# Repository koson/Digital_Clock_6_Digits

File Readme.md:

# Digital Clock 6 Digits

## คำแนะนำ
สร้างนาฬิกา Digital 6 Digit โดยใช้อุปกรณ์ที่เรียนในวิชา เพื่อแสดงเวลาในรูปแบบ HH:MM:SS โดยใช้หลักการทำงานของวงจร Digital Logic และ Counter 

โครงงานนี้ใช้วิธีการเดินสายด้วย Wire wrapping เพื่อลดขั้นตอนในการทำ PCB และเป็นการฝึกให้นักศึกษาได้บัดกรีวงจรที่มีความซับซ้อนในระดับที่เหมาะสม

รูปตัวอย่างของบอร์ดทั้งหมด ไม่ได้เป็นข้อบังคับให้นักศึกษาต้องทำให้เหมือน อีกทั้งนักศึกษาสามารถเพิ่มเติมฟังก์ชันที่ดีกว่าต้นฉบับได้ แต่ไม่ควรน้อยกว่าเป็นอันขาด

ไฟล์ทั้งหมดที่ใช้อธิบายการทำงานและสร้างโครงงาน อยู่ในโฟลเดอร์ Documents

#### ถ้ามีข้อสงสัยหรือต้องการคำอธิบายเพิ่ม ให้เปิด issue มาได้เลยนะครับ

## 🆘 ขี้เกียจอ่านยาว ๆ  เชิญทางนี้เลยครับ [🛝](./Documents/Short-Docs.md) 

## 🆘 หรือไม่อยากอ่านเลย อยากดูคลิปอย่างเดียว  ก็เชิญทางนี้เลยครับ [🎞️](./Documents/Video-Links.md) 

---

## 📐 สถาปัตยกรรม Hardware แบบ MVC (Model-View-Controller)

โปรเจคนี้ออกแบบโดยแบ่งส่วนการทำงานออกเป็น 3 ส่วนหลักตามแนวคิด MVC:

### 🎮 **Controller** - ส่วนควบคุมและสร้างสัญญาณ Clock
- **หน้าที่:** สร้างสัญญาณนาฬิกา (Clock Signal) ที่ความถี่ 1 Hz (1 วินาที/รอบ) พร้อมทั้งสวิตช์กดเพื่อการตั้งเวลา
- **อุปกรณ์หลักส่วนกำเนิดสัญญาณนาฬิกา:** 
  - NE555 Timer ในโหมด Astable เพื่อสร้าง Clock pulse
  - LED และตัวต้านทาน  
- **ผลลัพธ์:** สัญญาณ Clock ที่มีความแม่นยำสำหรับนับเวลา สามารถสังเกตุการทำงานจากการกระพริบของ LED

- **อุปกรณ์หลักส่วนตั้งเวลาสำหรับนาฬิกา:** 
  - สวิตช์กด push button ชนิด กดติดปล่อยดับ
  - ตัวต้านทาน  Pull-up หรือ Pull Down
  - ตัวเก็บประจุ debouncing
  - SN7414 Schmitt Trigger สำหรับปรับสัญญาณให้เสถียร
  - SN7474 D Flip-Flop สำหรับสลับโหมด (RUN/SETTIME)
  - SN74LS157 Multiplexer สำหรับเลือกเส้นทางสัญญาณสำหรับโหมด  RUN และ SETTIME
- **ผลลัพธ์:** การกดปุ่มแต่ละครั้ง ไม่มี bounce และสามารถเปลี่ยนโหมด (RUN/SETTIME) และเพิ่มค่าในหลัก HH:MM:SS ครั้งละ 1 ได้ตามต้องการ 

### 📊 **Model** - ส่วนประมวลผลและนับเวลา (Counters)
- **หน้าที่:** นับและจัดเก็บค่าเวลา (ชั่วโมง นาที วินาที) ในรูปแบบ BCD
- **อุปกรณ์หลัก:**
  - SN74LS390 Decade Counter (นับเลข 0-9 และ 0-5)
- **โครงสร้างการนับ:**
  - วินาทีหลักหน่วย: 0-9 (ใช้ Counter mod-10)
  - วินาทีหลักสิบ: 0-5 (ใช้ Counter mod-6)
  - นาทีหลักหน่วย: 0-9 (ใช้ Counter mod-10)
  - นาทีหลักสิบ: 0-5 (ใช้ Counter mod-6)
  - ชั่วโมงหลักหน่วย: 0-9 (ใช้ Counter mod-10)
  - ชั่วโมงหลักสิบ: 0-2 (ใช้ Counter mod-3 สำหรับรูปแบบ 24 ชั่วโมง)

### 🖥️ **View** - ส่วนแสดงผล (7 Segments)
- **หน้าที่:** แสดงค่าเวลาออกทาง 7-Segment Display
- **อุปกรณ์หลัก:**
  - CD4543 BCD-to-7-Segment Decoder (6 ตัว สำหรับแต่ละหลัก)
  - 7-Segment Display Common Cathode (6 หลัก)
- **การทำงาน:** รับค่า BCD จาก Model แปลงเป็นรหัส 7-Segment เพื่อแสดงผลตัวเลข 0-9

---

## 🔧 การทำงานของแต่ละส่วนในโปรเจค

### 1. ส่วน Clock Generator (NE555)
- สร้างสัญญาณสี่เหลี่ยมความถี่ ~1 Hz
- ใช้สูตรคำนวณ: $f = \frac{1.44}{(R_1 + 2R_2) \times C}$
- ค่าที่ใช้: R1 = 1kΩ, R2 = 6.8kΩ, C = 100µF
- ความถี่ที่ได้: 0.986 Hz (ความคลาดเคลื่อน 1.4%)

### 2. ส่วน Counter (SN74LS390)
**วินาที:**
- Counter ตัวที่ 1: นับหลักหน่วย 0→9 (mod-10)
- Counter ตัวที่ 2: นับหลักสิบ 0→5 (mod-6)
- เมื่อครบ 59 วินาที Reset และส่งสัญญาณ Carry ไปยังส่วนนาที

**นาที:**
- Counter ตัวที่ 3: นับหลักหน่วย 0→9 (mod-10)
- Counter ตัวที่ 4: นับหลักสิบ 0→5 (mod-6)
- เมื่อครบ 59 นาที Reset และส่งสัญญาณ Carry ไปยังส่วนชั่วโมง

**ชั่วโมง:**
- Counter ตัวที่ 5: นับหลักหน่วย 0→9 (mod-10)
- Counter ตัวที่ 6: นับหลักสิบ 0→2 (mod-3)
- เมื่อครบ 23:59:59 Reset กลับเป็น 00:00:00

### 3. ส่วน Display (CD4543 + 7-Segment)
- รับสัญญาณ BCD 4 บิตจาก Counter แต่ละหลัก
- CD4543 ทำหน้าที่แปลง BCD เป็นสัญญาณควบคุม 7-Segment (a-g)
- แสดงผลตัวเลข 0-9 บน 7-Segment Display

### 4. ส่วน Time Setting
- Switch สำหรับหยุดนับและปรับเวลา
- Push Button สำหรับตั้งค่าชั่วโมง/นาที/วินาที

---

## 📁 คำอธิบายไฟล์ในโปรเจค

### 📄 Markdown Documents
- **`Readme.md`** - เอกสารหลักของโปรเจค อธิบายภาพรวมและวิธีการทำงาน
- **[`Bill-of-materials.md`](Documents/Bill-of-materials.md)** - รายการอุปกรณ์ที่ใช้ในโปรเจค
- **[`Construction-Process.md`](Construction-Process-Display.md)** - ขั้นตอนการประกอบวงจรตามลำดับ
- **[`Datasheets.md`](Documents/Datasheets.md)** - รายละเอียด Datasheet ของ IC ที่ใช้ในวงจร
- **[`Kicad-Setup.md`](Documents/Kicad-Setup.md)** - คู่มือการตั้งค่าและใช้งาน KiCad
- **[`NE555_Clock.md`](NE555-Clock-Generator.md)** - การคำนวณและออกแบบวงจร NE555

### 🔌 Circuit Files (โฟลเดอร์ Circuit/)
- **[`Digital_Clock_6_Digits.kicad_pro`](Circuit/Digital_Clock_6_Digits.kicad_pro)** - ไฟล์โปรเจค KiCad หลัก
- **[`Digital_Clock_6_Digits.kicad_sch`](Circuit/Digital_Clock_6_Digits.kicad_sch)** - Schematic หลักที่เชื่อมโยงส่วนย่อย
- **[`Controller.kicad_sch`](Circuit/Controller.kicad_sch)** - วงจร NE555 Clock Generator
- **[`Counter.kicad_sch`](Circuit/Counter.kicad_sch)** - วงจร Counter ทุกหลัก (วินาที นาที ชั่วโมง)
- **[`7Seg_6Digits.kicad_sch`](Circuit/7Seg_6Digits.kicad_sch)** - วงจร Decoder และ Display 6 หลัก
- **[`Seven_Segment_View.kicad_sch`](Circuit/Seven_Segment_View.kicad_sch)** - มุมมองการเชื่อมต่อ 7-Segment
- **[`Digital_Clock_6_Digits.kicad_pcb`](Circuit/Digital_Clock_6_Digits.kicad_pcb)** - ไฟล์ออกแบบ PCB
- **[`Library.kicad_sym`](Circuit/Library.kicad_sym)** - ไลบรารีสัญลักษณ์ที่ใช้ในโปรเจค
- **[`Digital_Clock_6_Digits.csv`](Circuit/Digital_Clock_6_Digits.csv)** - Bill of Materials จาก KiCad

---

## 🛠️ ลำดับขั้นตอนการทำโปรเจค

``` mermaid
%%{init: {'theme':'base', 'flowchart': {'padding': 20, 'nodeSpacing': 50, 'rankSpacing': 50}, 'themeVariables': {'fontSize':'13px', 'fontFamily':'Arial'}}}%%
flowchart TD
    Phase1["Study documentation"] --> Phase2["Study schematic in Kicad"]
    Phase2 --> Phase3["Acquire components"]   

    subgraph "building circuit"
        direction TB
        Phase4
        Phase5
        Phase6
    end
    Phase3 --> Phase4["Build Display circuit"]
    Phase4 --> Phase5["Build Counter circuit"]
    Phase5 --> Phase6["Build Controller circuit"]
    Phase6 --> Phase7["Test and Debug"]
    Phase7 --> Phase7-1{"Does it work?"}
    Phase7-1 -->|Yes| Phase8["Document and Publish"]
    Phase7-1 -->|No| Phase3["Acquire components"]
```

### Phase 1: ศึกษาเอกสารต่างๆ (เริ่มจากไฟล์ Readme.md)
- [ ] **ศึกษา Datasheet** ของ IC แต่ละตัวให้เข้าใจการทำงาน โดยเฉพาะ:
	- [ ] CD4543 (BCD-to-7-Segment Decoder)
	- [ ] SN74LS390 (Decade Counter)
	- [ ] NE555 (Timer)
	- [ ] SN74LS157 (Multiplexer)

- [ ] **ศึกษาวงจรย่อย** แต่ละส่วนที่อาจารย์ให้ไว้:
	- [ ] วงจร Clock Generator (NE555)
	- [ ] วงจร Counter (SN74LS390) สำหรับ วินาที นาที ชั่วโมง
    - [ ] วงจร Display (CD4543 + 7-Segment)

- [ ]  **คำนวณค่าอุปกรณ์:** ถ้าอุปกรณ์ที่หามาได้ไม่ตรงกับค่าในวงจร 
	- [ ]  คำนวณ R และ C สำหรับ NE555 ให้ได้ความถี่ 1 Hz
	- [ ]  ตรวจสอบ Duty Cycle ให้อยู่ในช่วง 40-60%

### Phase 2: ศึกษาวงจรใน KiCad (ต้องลงโปรแกรม KiCad)
- [ ] **สร้าง Schematic แยกตามส่วน:**
    - [ ] `Controller.kicad_sch` - วงจร NE555
    - [ ] `Counter.kicad_sch` - วงจรนับเวลา
    - [ ] `7Seg_6Digits.kicad_sch` - วงจรแสดงผล
    - [ ] `Digital_Clock_6_Digits.kicad_sch` - เชื่อมโยงทุกส่วนเข้าด้วยกัน

- [ ] **ตรวจสอบความถูกต้อง:**
    - [ ] ตรวจสอบการเชื่อมต่อระหว่างส่วน
    - [ ] ตรวจสอบ Power Supply (VCC, GND)
    - [ ] ใช้มัลติมิเตอร์ตรวจสอบข้อผิดพลาด

### Phase 3: จัดหาอุปกรณ์ตามรายการ
- [ ] **จัดทำรายการอุปกรณ์ (BOM - Bill of Materials):**
    - [ ] IC ทั้งหมดตาม Schematic (CD4543, SN74LS390, NE555, SN74LS157, SN7414, SN7474)
    - [ ] 7-Segment Display Common Cathode 6 หลัก ควรใส่ Socket หรือ connector ตามคำแนะนำในการประกอบวงจร
    - [ ] ตัวต้านทาน (Resistor) ค่าต่างๆ ตามที่คำนวณไว้ในวงจร
    - [ ] ตัวเก็บประจุ (Capacitor) สำหรับวงจร NE555 และ Decoupling
    - [ ] แผ่นวงจรเอนกประสงค์ (Universal PCB) ขนาดที่เหมาะสม
    - [ ] IC Socket สำหรับ IC ทุกตัว (แนะนำให้ใช้เพื่อความสะดวกในการเปลี่ยน IC)
    - [ ] สาย Wire Wrap หรือสายเดินสายแบบอ่อน (Jumper Wire)
    - [ ] Push Button Switch สำหรับตั้งค่าเวลา
    - [ ] LED สำหรับแสดงสถานะ Clock
    - [ ] แหล่งจ่ายไฟ 5V (Adapter หรือ Battery)

- [ ] **ตรวจสอบอุปกรณ์:**
    - [ ] ตรวจสอบความถูกต้องของ IC ทุกตัวด้วย Datasheet
    - [ ] ทดสอบค่าตัวต้านทานและตัวเก็บประจุด้วย Multimeter
    - [ ] ตรวจสอบ 7-Segment Display ว่าเป็น Common Cathode
    - [ ] เตรียมอุปกรณ์สำรอง (IC, ตัวต้านทาน, สาย) กรณีชำรุด

### Phase 4: ประกอบส่วน Display
- [ ] **เตรียมอุปกรณ์สำหรับส่วน Display:**
    - [ ] IC Socket สำหรับ CD4543 (6 ตัว)
    - [ ] CD4543 BCD-to-7-Segment Decoder (6 ตัว)
    - [ ] 7-Segment Display Common Cathode (6 หลัก)
    - [ ] ตัวต้านทาน Current Limiting สำหรับ LED แต่ละ Segment
    - [ ] แผ่นวงจรเอนกประสงค์ขนาดพอเหมาะ

- [ ] **วางตำแหน่ง Component:**
    - [ ] วาง 7-Segment Display ให้เรียงตามลำดับ (HH:MM:SS)
    - [ ] วาง IC Socket สำหรับ CD4543 ไว้ใกล้กับ 7-Segment แต่ละหลัก
    - [ ] วางตำแหน่งให้พิจารณาเส้นทางการเดินสายไปยัง Counter (ส่วนถัดไป)
    - [ ] สามารถวางตามตัวอย่างในรูปชิ้นงานที่สำเร็จแล้วได้ 

- [ ] **บัดกรี Component:**
    - [ ] บัดกรี 7-Segment Display ทั้ง 6 หลัก ตรวจสอบให้แน่ใจว่าหลักตรง
    - [ ] บัดกรี IC Socket สำหรับ CD4543 ทั้ง 6 ตัว ตรวจสอบทิศทางขา 1
    - [ ] บัดกรีตัวต้านทาน Current Limiting สำหรับแต่ละ Segment

- [ ] **เดินสายด้วย Wire Wrap:**
    - [ ] เชื่อมต่อสาย VCC และ GND ให้ทุก IC (ควรเดินสายเป็นแนว Bus)
    - [ ] เชื่อมต่อสาย Output a-g จาก CD4543 ไปยัง 7-Segment แต่ละหลัก
    - [ ] เชื่อมต่อขา Common Cathode ของ 7-Segment ทั้งหมดไปยัง GND
    - [ ] เตรียมจุดต่อสำหรับสาย Input BCD (4 บิต) จากส่วน Counter

- [ ] **ทดสอบส่วน Display:**
    - [ ] **ยังไม่ต้องใส่ CD4543 ลงใน IC Socket**
    - [ ] จ่ายไฟ 5V ตรวจสอบแรงดันที่ขาไฟเลี้ยงและ ground ของ IC ทุกตัว
    - [ ] ถ้าวัดไฟแล้วไม่มีอะไรผิดพลาด ให้ปลดไฟเลี้ยงออกแล้วเสียบ IC ลงไปใน socket โดยทำจากหลักวินาทีเพียงตัวเดียวก่อน
    - [ ] จ่ายไฟเข้าวงจร IC ต้องไม่ร้อนกว่าปกติ วัดแรงดันไฟเลี้ยงควรได้เท่ากับตอนที่ยังไม่เสียบ IC 
    - [ ] ทดสอบการแสดงผลด้วยการจ่ายสัญญาณ BCD แบบ Manual (ใช้สวิตช์หรือสาย Jumper)
    - [ ] ตรวจสอบว่าแต่ละหลักสามารถแสดงตัวเลข 0-9 ได้ถูกต้อง
    - [ ] บันทึกปัญหาที่พบ (ถ้ามี) เช่น Segment ที่ไม่ติด

### Phase 5: ประกอบส่วน Counter
- [ ] **เตรียมอุปกรณ์สำหรับส่วน Counter:**
    - [ ] IC Socket สำหรับ SN74LS390 (3 ตัว สำหรับ วินาที นาที ชั่วโมง)
    - [ ] SN74LS390 Dual Decade Counter (3 ตัว)
    - [ ] ตัวเก็บประจุ Decoupling 0.1µF สำหรับแต่ละ IC
    - [ ] แผ่นวงจรเอนกประสงค์ขนาดพอเหมาะ (หรือใช้แผ่นเดียวกับ Display)

- [ ] **วางตำแหน่ง Component:**
    - [ ] วาง IC Socket สำหรับ Counter ตามลำดับ: วินาที → นาที → ชั่วโมง
    - [ ] วางให้สะดวกต่อการเชื่อมต่อกับส่วน Display และ Controller
    - [ ] คำนึงถึงการเดินสายระหว่าง Counter แต่ละหลัก (Cascade)
    - [ ] สามารถวางตำแหน่งตามในรูปวงจรต้นแบบได้

- [ ] **บัดกรี Component:**
    - [ ] บัดกรี IC Socket สำหรับ SN74LS390 ทั้ง 3 ตัว
    - [ ] บัดกรีตัวเก็บประจุ Decoupling ไว้ใกล้ขา VCC และ GND ของแต่ละ IC
    - [ ] บัดกรี IC Logic Gate เพิ่มเติม (ถ้ามี) สำหรับวงจร Reset

- [ ] **เดินสายด้วย Wire Wrap:**
    - [ ] เชื่อมต่อสาย VCC และ GND ให้ทุก IC
    - [ ] **วงจรวินาที:** บัดกรีวงจรตามที่แสดงใน Kicad
        - [ ] เชื่อมต่อ Clock Input สำหรับนับวินาทีหลักหน่วย (0-9)
        - [ ] เชื่อมต่อ Carry Output ไปยังหลักสิบ (0-5)
        - [ ] ต่อขา Output BCD (4 บิต) ของทั้ง 2 หลักไปยังส่วน Display
        - [ ] ต่อวงจร Reset เมื่อครบ 59 → 00
    - [ ] **วงจรนาที:** บัดกรีวงจรตามที่แสดงใน Kicad
        - [ ] รับ Clock Input จาก Carry ของวินาทีหลักสิบ
        - [ ] เชื่อมต่อ Carry Output ไปยังหลักสิบ (0-5)
        - [ ] ต่อขา Output BCD ไปยังส่วน Display
        - [ ] ต่อวงจร Reset เมื่อครบ 59 → 00
    - [ ] **วงจรชั่วโมง:** บัดกรีวงจรตามที่แสดงใน Kicad
        - [ ] รับ Clock Input จาก Carry ของนาทีหลักสิบ
        - [ ] เชื่อมต่อหลักหน่วย (0-9) และหลักสิบ (0-2)
        - [ ] ต่อขา Output BCD ไปยังส่วน Display
        - [ ] ต่อวงจร Reset เมื่อครบ 23 → 00 (รูปแบบ 24 ชั่วโมง)

- [ ] **เชื่อมต่อส่วน Display เข้ากับ Connector ทั้ง 6 ตัว:**
    - [ ] ต่อสาย BCD Output จาก Counter แต่ละหลักไปยัง Input ของ CD4543
    - [ ] ตรวจสอบความถูกต้องของการต่อสาย (bit 0-3)

- [ ] **ทดสอบส่วน Counter:**
    - [ ] ใส่ IC SN74LS390 ลงใน IC Socket ทุกตัว
    - [ ] จ่ายไฟ 5V และตรวจสอบแรงดันที่ IC ทุกตัว
    - [ ] จ่ายสัญญาณ Clock แบบ Manual (กดปุ่มหรือใช้ Switch)
    - [ ] ตรวจสอบการนับของวินาที: 00 → 01 → ... → 09 → 10 → ... → 59 → 00
    - [ ] ตรวจสอบ Carry Signal ส่งต่อไปยังนาทีเมื่อวินาทีครบ 59
    - [ ] ตรวจสอบการนับของนาทีและชั่วโมงแบบเดียวกัน
    - [ ] ตรวจสอบว่าเมื่อครบ 23:59:59 แล้ว จะ Reset เป็น 00:00:00

### Phase 6: ประกอบส่วน Controller (Clock Generator และ Time Setting)
- [ ] **เตรียมอุปกรณ์สำหรับส่วน Controller:**
    - [ ] IC Socket สำหรับ NE555, SN7414, SN7474, SN74LS157
    - [ ] NE555 Timer IC
    - [ ] SN7414 Schmitt Trigger (สำหรับปรับสัญญาณ)
    - [ ] SN7474 D Flip-Flop (สำหรับสลับโหมด RUN/SETTIME)
    - [ ] SN74LS157 Multiplexer (สำหรับเลือกสัญญาณ Clock)
    - [ ] ตัวต้านทาน 1kΩ, 6.8kΩ (หรือค่าที่คำนวณได้)
    - [ ] ตัวเก็บประจุ 100µF (หรือค่าที่คำนวณได้)
    - [ ] Push Button Switch (สำหรับ Mode Switch, Hour, Minute, Second)
    - [ ] LED สำหรับแสดงสถานะ Clock และโหมด
    - [ ] ตัวต้านทาน Pull-up/Pull-down สำหรับปุ่ม
    - [ ] ตัวเก็บประจุ Debouncing สำหรับปุ่มกด
    - [ ] แผ่นวงจรเอนกประสงค์ขนาดพอเหมาะ

- [ ] **ส่วน Clock Generator (NE555):**
    - [ ] บัดกรี IC Socket สำหรับ NE555
    - [ ] บัดกรีตัวต้านทาน R1 (1kΩ) และ R2 (6.8kΩ)
    - [ ] บัดกรีตัวเก็บประจุ C (100µF)
    - [ ] บัดกรี LED และตัวต้านทาน Current Limiting
    - [ ] เดินสายตาม Schematic ของ NE555 Astable Mode
    - [ ] เชื่อม Output ของ NE555 ไปยัง SN7414 (Schmitt Trigger)

- [ ] **ส่วน Time Setting:**
    - [ ] บัดกรี Push Button ทั้งหมด (Mode, Hour, Minute, Second)
    - [ ] บัดกรีตัวต้านทาน Pull-up/Pull-down สำหรับปุ่มแต่ละตัว
    - [ ] บัดกรีตัวเก็บประจุ Debouncing ควบคู่กับปุ่ม
    - [ ] บัดกรี IC Socket สำหรับ SN7414, SN7474, SN74LS157
    - [ ] เดินสาย Output จากปุ่มผ่าน SN7414 เพื่อปรับสัญญาณให้เสถียร
    - [ ] เดินสายจาก SN7474 เพื่อสลับระหว่างโหมด RUN และ SETTIME
    - [ ] เดินสายจาก SN74LS157 เพื่อเลือก Clock Source:
        - [ ] โหมด RUN: ใช้สัญญาณจาก NE555 (1 Hz)
        - [ ] โหมด SETTIME: ใช้สัญญาณจากปุ่มกด (Manual Clock)

- [ ] **เชื่อมต่อกับส่วน Counter:**
    - [ ] ต่อ Output จาก Multiplexer (SN74LS157) ไปยัง Clock Input ของ Counter
    - [ ] ต่อสัญญาณจากปุ่ม Hour, Minute, Second ไปยัง Clock Input ของ Counter ที่เกี่ยวข้อง (ผ่าน Multiplexer)

- [ ] **ทดสอบส่วน Controller:**
    - [ ] **ทดสอบ NE555 Clock Generator:**
        - [ ] จ่ายไฟ 5V และสังเกตการกระพริบของ LED
        - [ ] ถ้าสามารถ ให้วัดความถี่ด้วย Oscilloscope หรือ Frequency Counter (ควรได้ ~1 Hz)
        - [ ] ถ้าสามารถ ให้วัด Duty Cycle ควรอยู่ในช่วง 40-60%
    - [ ] **ทดสอบ Push Button และ Debouncing:**
        - [ ] กดปุ่มแต่ละตัวและตรวจสอบว่าไม่มี Bounce (อาจจะใช้ Oscilloscope หรือ Logic Probe แต่จากการออกแบบวงจร ไม่ควรจะเกิด bounce ถ้าบัดกรีถูกต้อง)
        - [ ] ตรวจสอบว่า Schmitt Trigger ทำงานถูกต้อง
    - [ ] **ทดสอบ Mode Switch (RUN/SETTIME):**
        - [ ] กดปุ่ม Mode และตรวจสอบว่า D Flip-Flop สลับสถานะ
        - [ ] ตรวจสอบว่า LED แสดงโหมดปัจจุบัน (RUN หรือ SETTIME)
    - [ ] **ทดสอบ Multiplexer:**
        - [ ] ในโหมด RUN: Counter ต้องนับตามสัญญาณจาก NE555 (1 วินาที/ครั้ง)
        - [ ] ในโหมด SETTIME: การกดปุ่ม Hour/Minute/Second ต้องเพิ่มค่าในหลักที่ถูกต้อง

### Phase 7: การทดสอบและแก้ไขปัญหา (Testing & Debugging)
- [ ] **ทดสอบการทำงานของแต่ละส่วนร่วมกัน:**
    - [ ] เชื่อมต่อทุกส่วนเข้าด้วยกัน: Controller → Counter → Display
    - [ ] จ่ายไฟ 5V และตรวจสอบแรงดันที่ IC ทุกตัว (ควรได้ 4.75-5.25V)
    - [ ] สังเกตการแสดงผลบน 7-Segment Display

- [ ] **ทดสอบโหมด RUN (การทำงานปกติ):**
    - [ ] ตั้งเวลาเริ่มต้นเป็น 00:00:00
    - [ ] สังเกตการนับวินาที ควรเพิ่มทีละ 1 ทุกวินาที
    - [ ] ตรวจสอบการ Carry: 00:00:59 → 00:01:00, 00:59:59 → 01:00:00
    - [ ] ทดสอบการ Reset เมื่อครบ 23:59:59 → 00:00:00
    - [ ] ให้วงจรทำงานต่อเนื่อง 1-2 ชั่วโมง เพื่อตรวจสอบความเสถียร

- [ ] **ทดสอบโหมด SETTIME (การตั้งเวลา):**
    - [ ] กดปุ่ม Mode เพื่อเข้าสู่โหมด SETTIME
    - [ ] กดปุ่ม Hour และตรวจสอบว่าชั่วโมงเพิ่มขึ้น
    - [ ] กดปุ่ม Minute และตรวจสอบว่านาทีเพิ่มขึ้น
    - [ ] กดปุ่ม Second และตรวจสอบว่าวินาทีเพิ่มขึ้น
    - [ ] กดปุ่ม Mode อีกครั้งเพื่อกลับสู่โหมด RUN
    - [ ] ตรวจสอบว่านาฬิกานับต่อจากเวลาที่ตั้งไว้

- [ ] **ทดสอบความแม่นยำของเวลา:**
    - [ ] เปรียบเทียบกับนาฬิกามาตรฐาน (นาฬิกาข้อมือ, โทรศัพท์)
    - [ ] ให้วงจรทำงานต่อเนื่อง 24 ชั่วโมง
    - [ ] วัดความคลาดเคลื่อนของเวลา (ควรไม่เกิน ±1-2 นาที/วัน)
    - [ ] หากความคลาดเคลื่อนมาก ให้ปรับค่า R หรือ C ของ NE555

- [ ] **การแก้ไขปัญหาทั่วไป:**
    - [ ] **Display ไม่แสดงผล:**
        - [ ] ตรวจสอบการต่อขา IC และ 7-Segment
        - [ ] ตรวจวัดแรงดันที่ขา VCC และ GND
        - [ ] ตรวจสอบตัวต้านทาน Current Limiting
    - [ ] **Counter นับไม่ถูกต้อง:**
        - [ ] ตรวจสอบสัญญาณ Clock ด้วย Oscilloscope หรือ Logic Probe
        - [ ] ตรวจสอบวงจร Reset (อาจ Reset บ่อยเกินไปหรือไม่ Reset)
        - [ ] ตรวจสอบการต่อ Carry Signal ระหว่าง Counter
    - [ ] **Clock ความถี่ไม่ถูกต้อง:**
        - [ ] วัดค่าจริงของ R และ C ด้วย Multimeter
        - [ ] คำนวณความถี่ใหม่และปรับค่า R หรือ C
        - [ ] ตรวจสอบการต่อวงจร NE555
    - [ ] **ปุ่มกดมี Bounce:**
        - [ ] เพิ่มตัวเก็บประจุ Debouncing (0.1-1µF)
        - [ ] ตรวจสอบวงจร Schmitt Trigger
    - [ ] **นาฬิกาหยุดทำงานหลังทำงานได้สักพัก:**
        - [ ] ตรวจสอบการบัดกรีที่หลวม (Cold Solder Joint)
        - [ ] ตรวจสอบแหล่งจ่ายไฟว่ามีกระแส (Current) เพียงพอ
        - [ ] เพิ่มตัวเก็บประจุ Decoupling ที่ IC ทุกตัว

### Phase 8: เอกสารและการสรุปผล (Documentation)
- [ ] **ถ่ายภาพและวิดีโอ:**
    - [ ] ถ่ายภาพวงจรที่ประกอบเสร็จจากหลายมุม
    - [ ] ถ่ายภาพ Close-up ของแต่ละส่วนสำคัญ (Display, Counter, Controller)
    - [ ] ถ่ายภาพการเดินสายด้วย Wire Wrap
    - [ ] ถ่ายวิดีโอการทำงานของนาฬิกา ให้เห็นการเปลี่ยนวินาที 57 --> 58 --> 59 --> 00 --> 01 (อย่างน้อย 5 นาที) ทั้งในหลัก วินาที  --> นาที, นาที --> ชั่วโมง และเมื่อเปลี่ยน 23:59:xx ไปเป็น 00:00:xx
    - [ ] ถ่ายวิดีโอการตั้งเวลา (แสดงการใช้งานปุ่มกด)

- [ ] **บันทึกข้อมูลทางเทคนิค:**
    - [ ] รายการ IC ทั้งหมดที่ใช้พร้อมรุ่นและจำนวน
    - [ ] ค่าตัวต้านทานและตัวเก็บประจุที่ใช้จริง
    - [ ] ค่าความถี่ของ Clock ที่วัดได้
    - [ ] ความคลาดเคลื่อนของเวลาที่วัดได้
    - [ ] BOM (Bill of Materials) ฉบับสมบูรณ์

- [ ] **บันทึกปัญหาและวิธีแก้ไข:**
    - [ ] ปัญหาที่พบระหว่างการประกอบและทดสอบ
    - [ ] วิธีการแก้ไขปัญหาแต่ละอย่าง
    - [ ] ข้อผิดพลาดที่เกิดขึ้นและบทเรียนที่ได้รับ
    - [ ] คำแนะนำสำหรับผู้ที่จะทำโปรเจคนี้ต่อไป

- [ ] **เขียนเอกสารสรุป:**
    - [ ] วัตถุประสงค์ของโปรเจค
    - [ ] หลักการทำงานของนาฬิกา Digital
    - [ ] การออกแบบวงจรและการคำนวณ
    - [ ] ขั้นตอนการประกอบโดยสังเขป
    - [ ] ผลการทดสอบและประเมินความสำเร็จ
    - [ ] สรุปและข้อเสนอแนะ

- [ ] **เผยแพร่บน GitHub (ถ้าต้องการ):**
    - [ ] อัพโหลดไฟล์ Schematic (KiCad)
    - [ ] อัพโหลดรูปภาพ
    - [ ] อัพโหลดวิดีโอขึ้น YouTube และแปะลิ้งค์ไว้บน Github
    - [ ] อัพเดต README.md ให้มีข้อมูลครบถ้วน
    - [ ] เพิ่ม Bill of Materials (BOM)
    - [ ] เพิ่มคู่มือการประกอบ (Construction Process)
    - [ ] เขียน License และ Contributors
    - [ ] เปิดให้ผู้สนใจสามารถเปิด Issue หรือ Pull Request ได้

---

## 📚 เอกสารอ้างอิง
- [Bill of Materials](./Documents/Bill-of-materials.md) - รายการอุปกรณ์
- [Construction Process](./Documents/Construction-Process-Display.md) - ขั้นตอนการประกอบ
- [Datasheets](./Documents/Datasheets.md) - ข้อมูล IC ที่ใช้
- [NE555 Clock Calculation](./Documents/NE555-Clock-Generator.md) - การคำนวณวงจร Clock

---

## วงจรที่ประกอบสำเร็จแล้ว

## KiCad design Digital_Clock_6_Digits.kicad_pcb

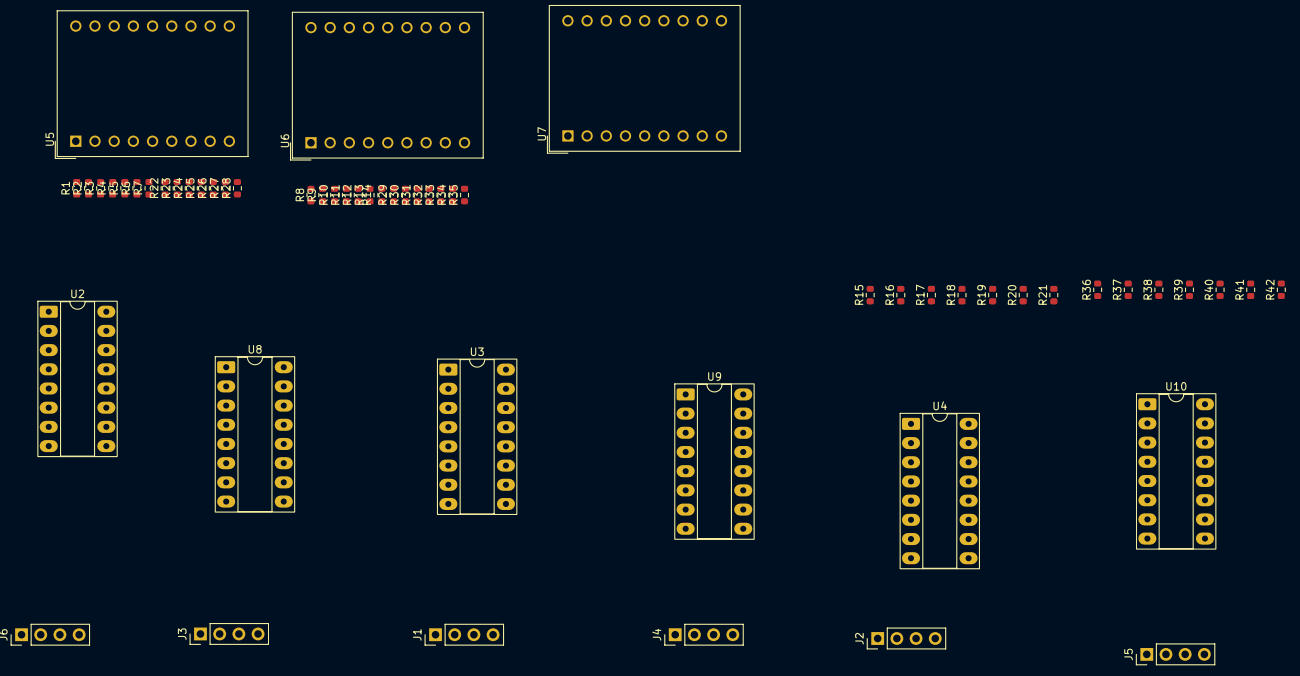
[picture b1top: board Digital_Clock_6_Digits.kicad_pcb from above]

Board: 2 copper layers, 57 parts (0 on the bottom side), 110 nets, no tracks yet.

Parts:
J1, J2, J3, J4, J5, J6: Conn_01x04; PinHeader_1x04_P2.54mm_Vertical
R1, R2, R3, R4, R5, R6, R7, R8, R9, R10, R11, R12, R13, R14, R15, R16, R17, R18, R19, R20, R21, R22, R23, R24, R25, R26, R27, R28, R29, R30, R31, R32, R33, R34, R35, R36, R37, R38, R39, R40, R41, R42: 220; R_0603_1608Metric
U2, U3, U4, U8, U9, U10: 4543; DIP-16_W7.62mm_Socket_LongPads
U5, U6, U7: DA56-11SURKWA; DA56-11CGKWA

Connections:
+5V: U2.1 (~LE), U2.16 (VDD), U3.1 (~LE), U3.16 (VDD), U4.1 (~LE), U4.16 (VDD), U8.1 (~LE), U8.16 (VDD), U9.1 (~LE), U9.16 (VDD), U10.1 (~LE), U10.16 (VDD)
/7Seg_6Digits/Seven_Segment_View/1H_D0: J3.1, U8.5 (D0)
/7Seg_6Digits/Seven_Segment_View/1H_D1: J3.2, U8.3 (D1)
/7Seg_6Digits/Seven_Segment_View/1H_D2: J3.3, U8.2 (D2)
/7Seg_6Digits/Seven_Segment_View/1H_D3: J3.4, U8.4 (D3)
/7Seg_6Digits/Seven_Segment_View/1M_D0: J4.1, U9.5 (D0)
/7Seg_6Digits/Seven_Segment_View/1M_D1: J4.2, U9.3 (D1)
/7Seg_6Digits/Seven_Segment_View/1M_D2: J4.3, U9.2 (D2)
/7Seg_6Digits/Seven_Segment_View/1M_D3: J4.4, U9.4 (D3)
/7Seg_6Digits/Seven_Segment_View/1S_D0: J5.1, U10.5 (D0)
/7Seg_6Digits/Seven_Segment_View/1S_D1: J5.2, U10.3 (D1)
/7Seg_6Digits/Seven_Segment_View/1S_D2: J5.3, U10.2 (D2)
/7Seg_6Digits/Seven_Segment_View/1S_D3: J5.4, U10.4 (D3)
/7Seg_6Digits/Seven_Segment_View/10H_D0: J6.1, U2.5 (D0)
/7Seg_6Digits/Seven_Segment_View/10H_D1: J6.2, U2.3 (D1)
/7Seg_6Digits/Seven_Segment_View/10H_D2: J6.3, U2.2 (D2)
/7Seg_6Digits/Seven_Segment_View/10H_D3: J6.4, U2.4 (D3)
/7Seg_6Digits/Seven_Segment_View/10M_D0: J1.1, U3.5 (D0)
/7Seg_6Digits/Seven_Segment_View/10M_D1: J1.2, U3.3 (D1)
/7Seg_6Digits/Seven_Segment_View/10M_D2: J1.3, U3.2 (D2)
/7Seg_6Digits/Seven_Segment_View/10M_D3: J1.4, U3.4 (D3)
/7Seg_6Digits/Seven_Segment_View/10S_D0: J2.1, U4.5 (D0)
/7Seg_6Digits/Seven_Segment_View/10S_D1: J2.2, U4.3 (D1)
/7Seg_6Digits/Seven_Segment_View/10S_D2: J2.3, U4.2 (D2)
/7Seg_6Digits/Seven_Segment_View/10S_D3: J2.4, U4.4 (D3)
GND: U2.6 (PH), U2.7 (BL), U2.8 (VSS), U3.6 (PH), U3.7 (BL), U3.8 (VSS), U4.6 (PH), U4.7 (BL), U4.8 (VSS), U5.13 (DIG2_CC), U5.14 (DIG1_CC), U6.13 (DIG2_CC), U6.14 (DIG1_CC), U7.13 (DIG2_CC), U7.14 (DIG1_CC), U8.6 (PH), U8.7 (BL), U8.8 (VSS), U9.6 (PH), U9.7 (BL), U9.8 (VSS), U10.6 (PH), U10.7 (BL), U10.8 (VSS)
unnamed: R1.1, U2.9 (Qa)
unnamed: R2.1, U2.10 (Qb)
unnamed: R3.1, U2.11 (Qc)
unnamed: R4.1, U2.12 (Qd)
unnamed: R5.1, U2.13 (Qe)
unnamed: R6.1, U2.15 (Qf)
unnamed: R7.1, U2.14 (Qg)
unnamed: R8.1, U3.9 (Qa)
unnamed: R9.1, U3.10 (Qb)
unnamed: R10.1, U3.11 (Qc)
unnamed: R11.1, U3.12 (Qd)
unnamed: R12.1, U3.13 (Qe)
unnamed: R13.1, U3.15 (Qf)
unnamed: R14.1, U3.14 (Qg)
unnamed: R15.1, U4.9 (Qa)
unnamed: R16.1, U4.10 (Qb)
unnamed: R17.1, U4.11 (Qc)
unnamed: R18.1, U4.12 (Qd)
unnamed: R19.1, U4.13 (Qe)
unnamed: R20.1, U4.15 (Qf)
unnamed: R21.1, U4.14 (Qg)
unnamed: R1.2, U5.16 (DIG1_A)
unnamed: R2.2, U5.15 (DIG1_B)
unnamed: R3.2, U5.3 (DIG1_C)
unnamed: R4.2, U5.2 (DIG1_D)
unnamed: R5.2, U5.1 (DIG1_E)
unnamed: R6.2, U5.18 (DIG1_F)
unnamed: R7.2, U5.17 (DIG1_G)
unnamed: R22.2, U5.11 (DIG2_A)
unnamed: R23.2, U5.10 (DIG2_B)
unnamed: R24.2, U5.8 (DIG2_C)
unnamed: R25.2, U5.6 (DIG2_D)
unnamed: R26.2, U5.5 (DIG2_E)
unnamed: R27.2, U5.12 (DIG2_F)
unnamed: R28.2, U5.7 (DIG2_G)
unnamed: R8.2, U6.16 (DIG1_A)
unnamed: R9.2, U6.15 (DIG1_B)
unnamed: R10.2, U6.3 (DIG1_C)
unnamed: R11.2, U6.2 (DIG1_D)
unnamed: R12.2, U6.1 (DIG1_E)
unnamed: R13.2, U6.18 (DIG1_F)
unnamed: R14.2, U6.17 (DIG1_G)
unnamed: R29.2, U6.11 (DIG2_A)
unnamed: R30.2, U6.10 (DIG2_B)
unnamed: R31.2, U6.8 (DIG2_C)
unnamed: R32.2, U6.6 (DIG2_D)
unnamed: R33.2, U6.5 (DIG2_E)
unnamed: R34.2, U6.12 (DIG2_F)
unnamed: R35.2, U6.7 (DIG2_G)
unnamed: R15.2, U7.16 (DIG1_A)
unnamed: R16.2, U7.15 (DIG1_B)
unnamed: R17.2, U7.3 (DIG1_C)
unnamed: R18.2, U7.2 (DIG1_D)
unnamed: R19.2, U7.1 (DIG1_E)
unnamed: R20.2, U7.18 (DIG1_F)
unnamed: R21.2, U7.17 (DIG1_G)
unnamed: R36.2, U7.11 (DIG2_A)
unnamed: R37.2, U7.10 (DIG2_B)
unnamed: R38.2, U7.8 (DIG2_C)
unnamed: R39.2, U7.6 (DIG2_D)
unnamed: R40.2, U7.5 (DIG2_E)
unnamed: R41.2, U7.12 (DIG2_F)
unnamed: R42.2, U7.7 (DIG2_G)
unnamed: R22.1, U8.9 (Qa)
unnamed: R23.1, U8.10 (Qb)
unnamed: R24.1, U8.11 (Qc)
unnamed: R25.1, U8.12 (Qd)
unnamed: R26.1, U8.13 (Qe)
unnamed: R27.1, U8.15 (Qf)
unnamed: R28.1, U8.14 (Qg)
unnamed: R29.1, U9.9 (Qa)
unnamed: R30.1, U9.10 (Qb)
unnamed: R31.1, U9.11 (Qc)
unnamed: R32.1, U9.12 (Qd)
unnamed: R33.1, U9.13 (Qe)
unnamed: R34.1, U9.15 (Qf)
unnamed: R35.1, U9.14 (Qg)
unnamed: R36.1, U10.9 (Qa)
unnamed: R37.1, U10.10 (Qb)
unnamed: R38.1, U10.11 (Qc)
unnamed: R39.1, U10.12 (Qd)
unnamed: R40.1, U10.13 (Qe)
unnamed: R41.1, U10.15 (Qf)
unnamed: R42.1, U10.14 (Qg)

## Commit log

2026-01-31 Add KiCad project files for 6-digit clock
    Add initial KiCad project for Digital_Clock_6_Digits: schematic (.kicad_sch), PCB (.kicad_pcb) and project file (.kicad_pro). Also add .gitignore to ignore KiCad lock files (*.lck) and .vscode. Files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
2026-01-31 Add backup files and create project settings for Digital Clock 6 Digits
    - Added a backup zip file containing project files and settings.
    - Created a new KiCad project settings file (Digital_Clock_6_Digits.kicad_prl) with configuration for board visibility, selection filters, and net inspector panel settings.
2026-02-03 Refactor code structure for improved readability and maintainability
    add Top lecvel and 6 Digits view
2026-02-03 Refactor code structure for improved readability and maintainability
2026-02-04 Add 74LS192 counter and project links
    Add a 74LS192 symbol definition and instance to Counter.kicad_sch (includes pins, properties and a U1 instance). Update Digital_Clock_6_Digits.kicad_pro to register Controller, Seven_Segment_View and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
2026-02-09 Add initial component list for Digital Clock project
    - Created a new CSV file 'Digital_Clock_6_Digits.csv' to define components.
    - Included details such as designators, footprints, quantities, and designations for resistors, connectors, and ICs.
2026-02-09 uodate
2026-02-16 Reorganize circuit files into Circuit/ directory
    Move PCB, CSV, datasheet and project files into a new Circuit/ subdirectory, add multiple backup ZIPs under Circuit/Digital_Clock_6_Digits-backups, and add symbol library files (Library.bak, Library.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
2026-02-16 Fix typo in frequency calculation heading
    Correct a spelling mistake in Progression/NE555_Clock.md by changing the heading 'Frequency calculayion' to 'Frequency calculation'. No functional changes to content or formulas.
2026-02-16 Escape percent signs in NE555_Clock.md
    Fix Markdown/LaTeX rendering by adding an extra backslash before percent signs in math expressions and result lines in Progression/NE555_Clock.md. No numerical or calculation changes—only formatting 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
2026-02-16 Fix formatting issues in NE555 Clock documentation
2026-02-16 Add test cases for percent sign handling in NE555 Clock documentation
2026-02-16 Fix LaTeX formatting for error and duty cycle calculations in NE555 Clock documentation
2026-02-16 Fix LaTeX formatting in frequency and error calculations in NE555 Clock documentation
2026-02-16 Fix LaTeX formatting in error calculation in NE555 Clock documentation
2026-02-16 Fix LaTeX formatting in Duty Cycle calculation in NE555 Clock documentation
2026-02-16 Fix LaTeX formatting in frequency and duty cycle calculations in NE555 Clock documentation
2026-02-17 Add Circuit backup path to .gitignore
    Add /Circuit/Digital_Clock_6_Digits-backups to .gitignore to exclude the Circuit project's backup directory and prevent accidental commits of backup files.
2026-02-18 add Readme.md
2026-02-18 remove backup files
2026-02-18 Remove obsolete documentation files and add new project documentation
2026-02-18 Ignore .obsidian; update workspace and README
    Add .obsidian to .gitignore, adjust Obsidian workspace (lastOpenFiles ordering and added entries), and significantly revise Readme.md. The README changes remove the "Optional" label from Time Setting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
2026-02-18 Remove duplicate entry for Digital_Clock_6_Digits-backups in .gitignore
2026-02-18 Add Bill of Materials and Datasheets documentation; remove obsolete Datasheet file
2026-02-18 Replace NE555 Clock documentation with updated file; remove obsolete NE555_Clock.md
2026-02-18 Add quick reference and video links documentation for Digital Clock project
2026-02-18 Update Video-Links.md to include a link to the README
2026-02-18 chore: clean up empty code change sections in the changes log
2026-02-18 Enhance Kicad setup documentation with detailed instructions for Schematic Editor and Hierarchy Navigator
2026-02-18 Add images for soldering examples in Construction Process documentation
2026-02-18 Add Construction Process Time Setting documentation
2026-02-18 Add initial content for Construction Process Time Setting documentation
2026-02-18 Add preliminary documentation for Construction Process in Controller and Counter sections
2026-02-18 Fix links in reference section to point to the correct document paths
2026-02-18 Update link for NE555 Clock Calculation documentation to correct file path
2026-02-18 Fix image path in NE555 Clock Generator documentation
2026-02-18 Fix image paths in README to point to the correct Documents directory
2026-02-18 Remove redundant reference to the Construction Process document in the Counter assembly instructions
2026-02-18 Fix link to Counter Design document in assembly instructions
2026-02-18 Enhance Counter-Design documentation with improved formatting and additional explanatory content
2026-03-04 chore: clean up code structure and remove redundant changes
